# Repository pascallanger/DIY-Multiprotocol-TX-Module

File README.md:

# Multiprotocol TX Module

The **Multiprotocol Tx Module** (or **MULTI-Module**) is a 2.4GHz transmitter module which enables almost any transmitter to control many different receivers and models, including many popular helicopters, planes, quadcopters, and miniquads.

The main forum for protocol requests and questions is on [RCGroups.com](https://www.rcgroups.com/forums/showthread.php?2165676-DIY-Multiprotocol-TX-Module/page10000).

If you like this project and want to support further development please consider making a [donation](docs/Donations.md).  

<table cellspacing=0>
  <tr>
    <td align=center width=200><br><b>€5</b></td>
    <td align=center width=200><br><b>€10</b></td>
    <td align=center width=200><br><b>€15</b></td>
    <td align=center width=200><br><b>€25</b></td>
    <td align=center width=200><br><b>Other</b></td>
  </tr>
</table>

## Development status

Multiprotocol downloads: 

Current Multiprotocol code check status: . Download the latest **test** build [here](https://downloads.multi-module.org/latest-test/).

Current Multiprotocol boards check status: 

## Quicklinks
* [Download latest releases of the firmware](https://github.com/pascallanger/DIY-Multiprotocol-TX-Module/releases) and [instructions to upload .hex files](docs/Advanced_Manually_Setting_ATmega328_Fuses.md)
* [Forum on rcgroups](http://www.rcgroups.com/forums/showthread.php?t=2165676)
* [Available Protocols list](Protocols_Details.md)
* [The old documentation](docs/README-old.md)

## Outline of the documentation
1. Introduction (this page)
1. [Available protocols](Protocols_Details.md)
1. [Transmitters and serial/telemetry options](docs/Transmitters.md)
1. [Module Hardware options](docs/Hardware.md)
1. Compiling and programming the module
    * [Atmega328p Multiprotocol Module](docs/Compiling.md)
    * [STM32 Multiprotocol Module](docs/Compiling_STM32.md)
    * [OrangeRX Module](docs/Compiling_OrangeTx.md)
1. [Transmitter Setup](docs/Transmitters.md) 
    * [Channel Order](docs/Channel_Order.md)
1. [How to for popular models](docs/Models.md)
1. [Troubleshooting](docs/Troubleshooting.md)
2. [Advanced Topics (not for the fainthearted!)](docs/Advanced_Topics.md)

## Introduction
A functioning MULTI-Module consists of (see image below):  

1.  A host RC Tx

1. A Multiprotocol Transmitter Module (MULTI-Module) that connects to a host transmitter.  This module is typically comprised of
   * A microcontroller (currently ATMega328P or STM32) that interfaces with the Tx, controls the module functions and forwards the RC commands to the RF hardware
   * One or more (but at least one) RF modules that provide the capability to communicate with RC receivers.  To communicate with the receiver the RF module in the Tx must match with the RF module type in the receiver.  The four most common 2.4GHz RF chips on the market are supported TI CC2500, Nordic NRF24L01, Cypress CYRF6936, and the Amiccom A7105
   * MULTI-firmware loaded on to the microprocessor.  At a high level, this firmware performs a few different functions: 
     * It interfaces with signals from the host Tx and decodes these for transmission to the model, it manages the activation of the correct hardware RF module for each protocol
     * It implements the unique communication protocols for each receiver/model and manages the all-important binding process with a receiver/model
     * In the case of some protocols (for example DSMX and FrSky) it receives and decodes the telemetry information and makes this available to the radio.
1. The physical 2.4GHz antenna (or in some cases multiple antennas) for the modules

One of the most attractive features of the MULTI-module is the ability to send telemetry signals back to the transmitter. The MULTI-Module is fully telemetry capable for all protocols that support telemetry.  Your ability to use the telemetry information depends on  your radio hardware and firmware.

In constructing a functioning MULTI-Module there are important choices to be made and tradeoffs to be aware of.  The most important are:

## **Choice 1:** Which MULTI-Module hardware option 

There are currently four generic paths to get your hands on an MULTI-Module.  These are outlined in detail on the [hardware](docs/Hardware.md) page.  Here they are, in order of increasing difficulty:
  - **Ready-made MULTI-Module** - Available from Banggood which includes a 4-in-1 RF module and an antenna switcher
  - **DIY MULTI-Module** - Purchase one of the PCB options from [OSHPark](http://www.oshpark.com) and then solder on your own components and RF modules (the two options differ in the MCU used - either an ATmega328P or a STM32F1)
  - **OrangeRx MULTI-Module** You can turn the OrangeRx DSM2/X Tx module (available from HobbyKing) into a MULTI-Module to increase the number of supported protocols, add telemetry as an option and bind more successfully with problematic bind-and-fly models. 
  - **Scratchbuild a MULTI-Module** -  Build the module from scratch using perfboard base, an Arduino Pro Mini and discrete components.

The last option is where it all started and how the pioneers in this project made their boards.  However, due to the growing interest in “one module to rule them all” you now have options to purchase a ready-made board (with old firmware that you will need to upgrade).  

For more information on these options see the [hardware](docs/Hardware.md) page

## **Choice 2:** Which RF modules to include in the MULTI-Module

This depends on your specific needs.  However, recent the availability of the 4-in-1 RF modules from Banggood for less than $35 makes it easy to “have it all”.  Most manufacturers of RC systems (Spektrum, FrSky, FlySky) and toys (Syma, Hubsan, etc.) use one of these four RF chips to manage the RF link between the transmitter and the reciever/model.  Here is an incomplete list of the RF modules and some of the most popular toys that use them.  For the complete list see the [Protocol Details](Protocols_Details.md) page.

|Manufacturer|RF Chip|Example Protocols|
|---|---|---|
|Cyprus Semiconductor|CYRF6936|DSM/DSMX|
|||Walkera Devo|
|||J6Pro|
|Texas Instruments|CC2500|FrSky|
|||Futaba SFHSS|
|Amiccom|A7105|FlySky|
|||FlySky AFHDS2A|
|||Hubsan|
|Nordic Semiconductor|NRF24L01|HiSky|
|||Syma|
|||ASSAN|
|||and most other Chinese models|

For example, if you have no interest in binding your Tx to an model with and FrSky or Futaba SFHSS receiver you do not need to include the CC2500 RF module in your system.

## **Choice 3:** Which protocols to upload to the MULTI-Module

As the list of supported protocols grows even the STM32 ARM microcontroller cannot hold all of the protocols. You can select the protocols you need and complie your own firmware. Fortunately, the process of selecting and compiling is not too difficult and it is fully documented on the [Compiling and Programming](docs/Compiling.md) page. You can also download firmware from the [Multi-Module](https://downloads.multi-module.org) website. These firmware files have been split into two groups, surface "SFC" and air "AIR". You can check which protocols are included in each of these groups in the [Validate.h](Multiprotocol/Validate.h) source file.

In the case of the ATmega328, the memory required by all the possible protocols exceeds the 32KB flash limit considerably. This means that you will need to make a choice of which protocols you will compile into your firmware.

## **Choice 4:** Choosing the type of interface between the MULTI-Module and your radio (PPM or Serial)

The MULTI-Module supports industry standard PPM interface that works with all transmitters with either:  
 - a module bay or
 - a trainer port or
 - any PPM signal that can be accessed inside the Tx.

Most of the older FM radios support the PPM interface.

If you are the owner of a transmitter that supports the er9X/erSky9X or OpenTX firmwares (Frsky Taranis, Horus or the FlySky TH9X or the Turnigy 9X family) you have the additional option to use a serial protocol to communicate between your Tx and the MULTI-Module. (Owners of Walkera Devo transmitters should look at the [Deviation Tx](http://www.deviationtx.com) project for how to achieve the same end goal). This serial protocol does not require any hardware modifications, but will likely require updating the firmware on your radio. For those willing to do this, there are some nice advantages:
  - The model protocol selection, associated parameters, failsafe and binding is done from the Model Settings menu on the Tx
  - For telemetry capable transmitters, the telemetry integration is done seamlessly with the Tx firmware. (Note that FrSky TH9X/Turnigy 9X/R transmitters require a telemetry mod to be done before telemetry can work).  Click on the link corresponding to your Tx on the [Transmitters](docs/Transmitters.md) page for more details.

# How to get started?
1. Browse the [Protocols](Protocols_Details.md) page to see which protocols you would like on your module
1. Go to the [Hardware Options](docs/Hardware.md) page to decide which of the MULTI-Module hardware options appeals to you and which RF modules you plan to integrate
1. Once you have your module, you should review what jumper settings or modifications are required to the module to support serial communication and possibly telemetry
1. Go to [Compiling and Programming](docs/Compiling.md) page to download, compile and program your MULTI-Module
1. Finally, you should visit the setup page for your transmitter by clicking on the link corresponding to your Tx on the [Transmitters](docs/Transmitters.md) page to configure the last few settings before you can fly to your heart’s content!!!!!

# Troubleshooting
Visit the [Troubleshooting](docs/Troubleshooting.md) page.  Please bear in mind that the MULTI-Module is a complex system of hardware and software and it may take some patience to get it up and running.  Also remember that the developers of the system are actual users of the system.  This means that at any moment in time the system is working perfectly for them.  A corollary to this is that if you are struggling there are likely two scenarios.  First, that the problem is with your hardware or with your configuration, second, and much more unlikely but not impossible scenario, is that you are struggling with a new undiscovered bug.  (The author of this documentation speaks from experience ;-)   Please check the RC Groups forum and search for keywords relating to your problem before posting a reply.  When you do post a reply please so humbly and respectfully – you will find many helpful people there.  In your reply please include as much relevant information as possible and attach compilation output and ```_Config.h``` files as text attachments to keep the forum clean.
# A final word
A very big thanks to all the people who have shared their time so graciously to create this great project.  If you come across them on RC Groups, please be kind and show appreciation.  In no particular order:
* Pascal Langer (rcgroups: hpnuts)
* Ben Lye (rcgroups: benzo99)
* Midelic (rcgroups: midelic)
* Mike Blandford (rcgroups: Mike Blandford)
* schwabe - from OpenTX 
* PhracturedBlue – from [Deviation TX project](http://www.deviationtx.com)
* goebish – from [Deviation TX project](http://www.deviationtx.com)
* victzh – from [Deviation TX project](http://www.deviationtx.com)
* hexfet – from [Deviation TX project](http://www.deviationtx.com)

Your help would be greatly appreciated.  If protocol reverse-engineering and dev is not your thing then any help with testing and contributing to the documentation would be amazing.  Given the number of different Tx/module hardware/RF module/protocol/model combinations the process of testing and documenting is a major bottleneck for the developers.  Anything you can do to help will free them up to do even greater things. 

If you like this project and want to support further development please consider making a [donation](docs/Donations.md).

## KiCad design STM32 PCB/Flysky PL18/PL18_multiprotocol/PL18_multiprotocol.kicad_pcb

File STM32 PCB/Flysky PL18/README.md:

# MPM for Flysky PL18

The PCB design is located in PL18_multiprotocol folder and is designed using KiCad 6.0.

The casing is located in Casing folder and is designed using Blender 3.3.1.  The model included 2 pieces, T is the top piece and B is the bottom pieces.  These 2 pieces is cloned into TF and BF respectively to apply all modifiers and make manifold for 3D printing.  I have included the stl files generated for simplity.

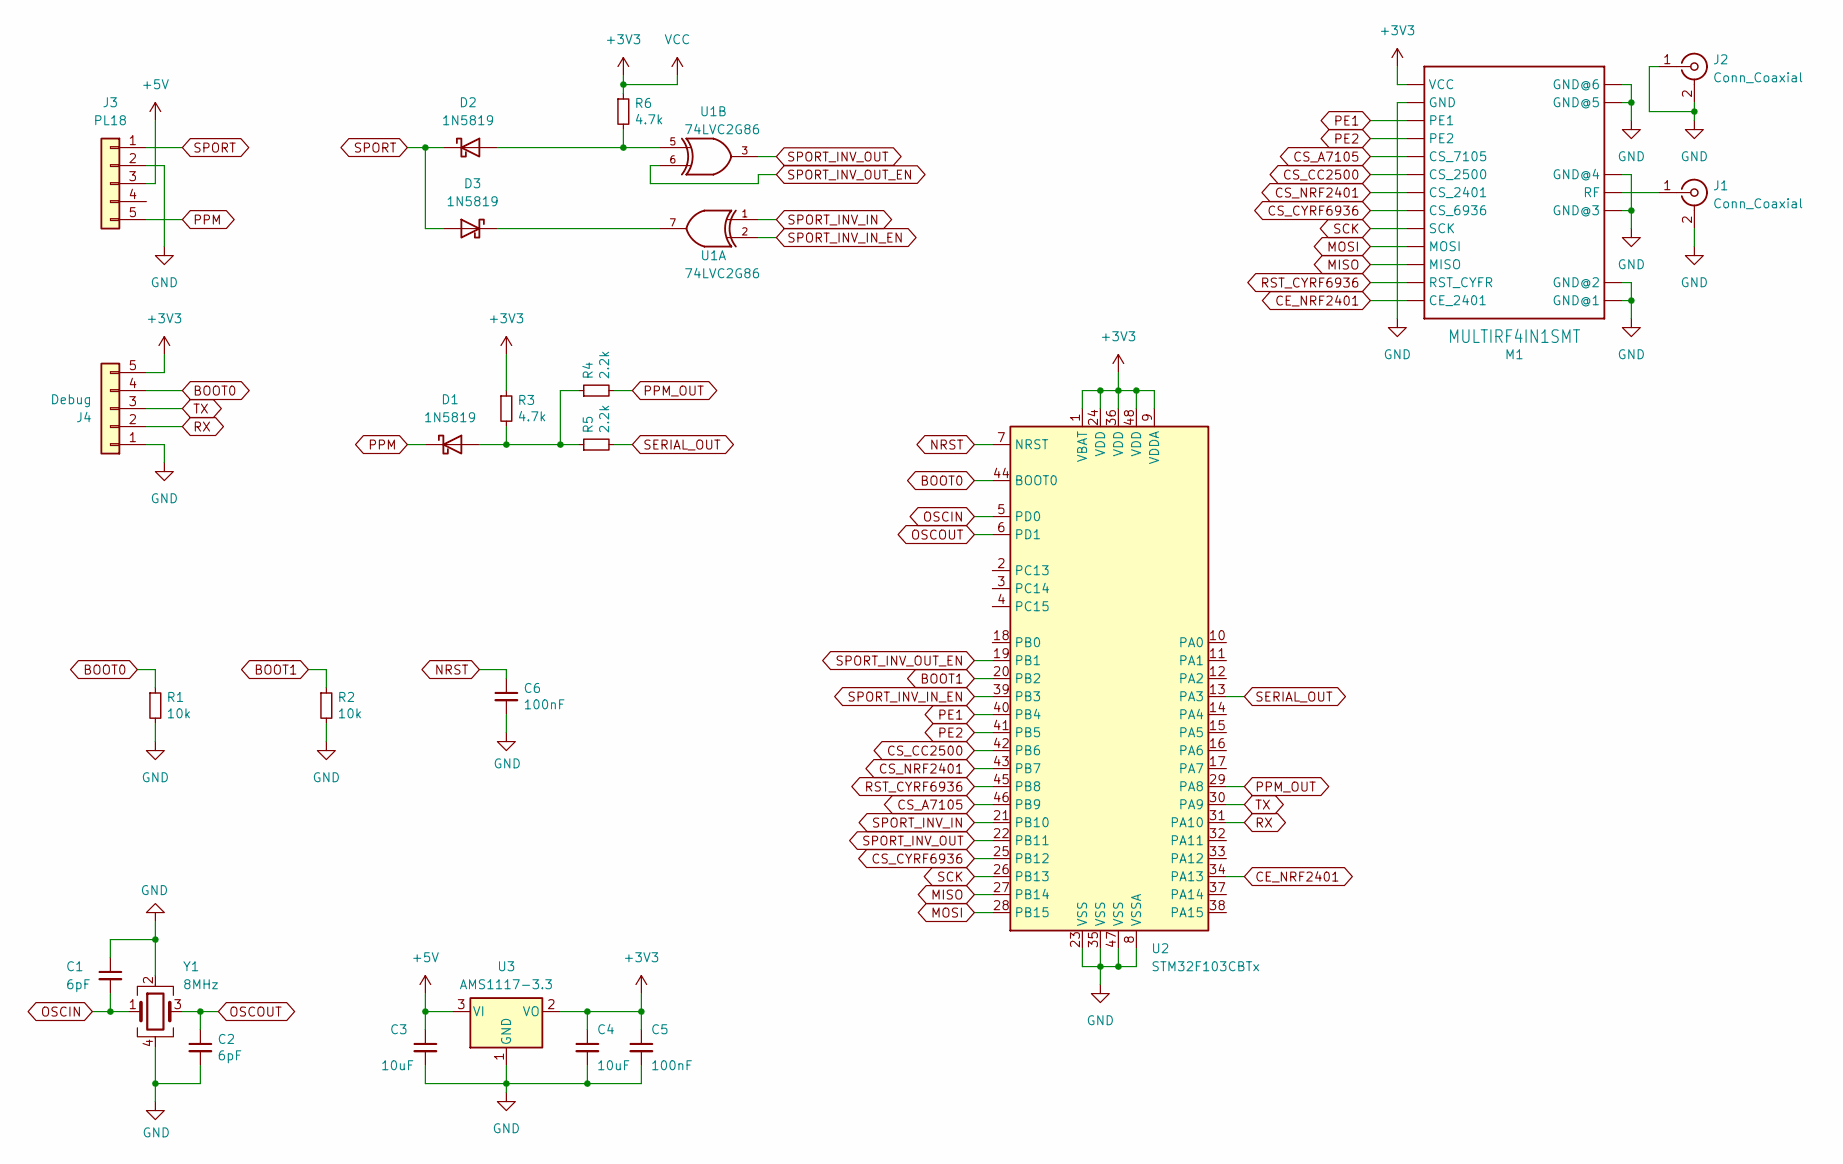
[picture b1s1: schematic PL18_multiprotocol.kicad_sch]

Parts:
C1, C2: 6pF; C_0603_1608Metric_Pad1.08x0.95mm_HandSolder
C3, C4: 10uF; C_0603_1608Metric_Pad1.08x0.95mm_HandSolder
C5, C6: 100nF; C_0603_1608Metric_Pad1.08x0.95mm_HandSolder
D1, D2, D3: 1N5819; D_SOD-123
J1, J2: Conn_Coaxial; MMCX_Molex_73415-1471_Vertical
J3: PL18; DS-B01F-A-S2
J4: Debug; JST_GH_BM05B-GHS-TBT_1x05-1MP_P1.25mm_Vertical
M1: MULTIRF4IN1SMT; MULTIRF4IN1-SMT
R1, R2: 10k; R_0603_1608Metric_Pad0.98x0.95mm_HandSolder
R3, R6: 4.7k; R_0603_1608Metric_Pad0.98x0.95mm_HandSolder
R4, R5: 2.2k; R_0603_1608Metric_Pad0.98x0.95mm_HandSolder
U1: 74LVC2G86; VSSOP-8_3.0x3.0mm_P0.65mm
U2: STM32F103CBTx; LQFP-48_7x7mm_P0.5mm
U3: AMS1117-3.3; SOT-223-3_TabPin2
Y1: 8MHz; Oscillator_SMD_Abracon_ASE-4Pin_3.2x2.5mm

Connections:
+3V3: C4.1, C5.1, J4.5, M1.VCC, R3.1, R6.1, U1.8 (VCC), U2.1 (VBAT), U2.9 (VDDA), U2.24 (VDD), U2.36 (VDD), U2.48 (VDD), U3.2 (VO)
+5V: C3.1, J3.3, U3.3 (VI)
BOOT0: J4.4, R1.1, U2.44 (BOOT0)
BOOT1: R2.1, U2.20 (PB2)
CE_NRF2401: M1.CE_2401, U2.34 (PA13)
CS_A7105: M1.CS_7105, U2.46 (PB9)
CS_CC2500: M1.CS_2500, U2.42 (PB6)
CS_CYRF6936: M1.CS_6936, U2.25 (PB12)
CS_NRF2401: M1.CS_2401, U2.43 (PB7)
GND: C1.1, C2.2, C3.2, C4.2, C5.2, C6.2, J1.2 (Ext), J2.1 (In), J2.2 (Ext), J3.2, J4.1, M1.GND, M1.GND@1, M1.GND@2, M1.GND@3, M1.GND@4, M1.GND@5, M1.GND@6, R1.2, R2.2, U1.4 (GND), U2.8 (VSSA), U2.23 (VSS), U2.35 (VSS), U2.47 (VSS), U3.1 (GND), Y1.2, Y1.4
MISO: M1.MISO, U2.27 (PB14)
MOSI: M1.MOSI, U2.28 (PB15)
NRST: C6.1, U2.7 (NRST)
unnamed: D1.2 (A), R3.2, R4.1, R5.1
unnamed: D2.2 (A), R6.2, U1.5
unnamed: D3.1 (K), U1.7
unnamed: J1.1 (In), M1.RF
OSCIN: C1.2, U2.5 (PD0), Y1.1
OSCOUT: C2.1, U2.6 (PD1), Y1.3
PE1: M1.PE1, U2.40 (PB4)
PE2: M1.PE2, U2.41 (PB5)
PPM: D1.1 (K), J3.5
PPM_OUT: R4.2, U2.29 (PA8)
RST_CYRF6936: M1.RST_CYFR, U2.45 (PB8)
RX: J4.2, U2.31 (PA10)
SCK: M1.SCK, U2.26 (PB13)
SERIAL_OUT: R5.2, U2.13 (PA3)
SPORT: D2.1 (K), D3.2 (A), J3.1
SPORT_INV_IN: U1.1, U2.21 (PB10)
SPORT_INV_IN_EN: U1.2, U2.39 (PB3)
SPORT_INV_OUT: U1.3, U2.22 (PB11)
SPORT_INV_OUT_EN: U1.6, U2.19 (PB1)
TX: J4.3, U2.30 (PA9)

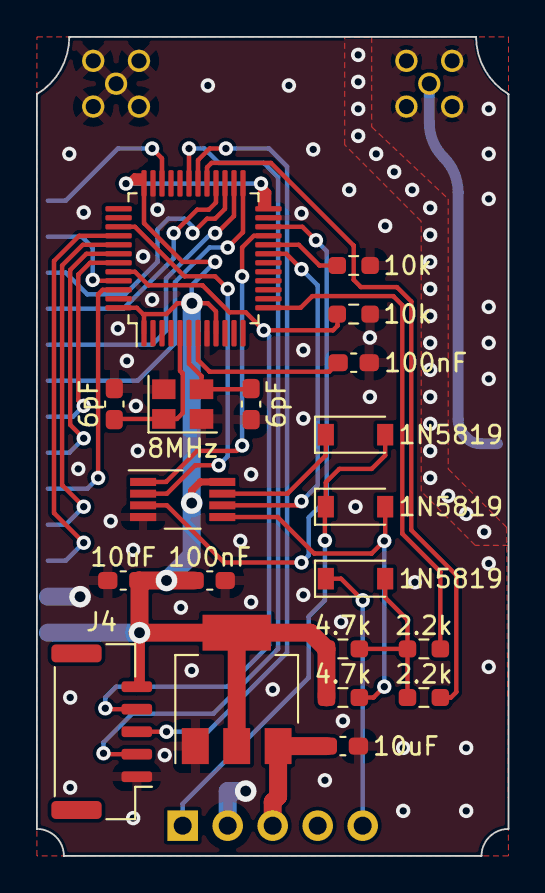
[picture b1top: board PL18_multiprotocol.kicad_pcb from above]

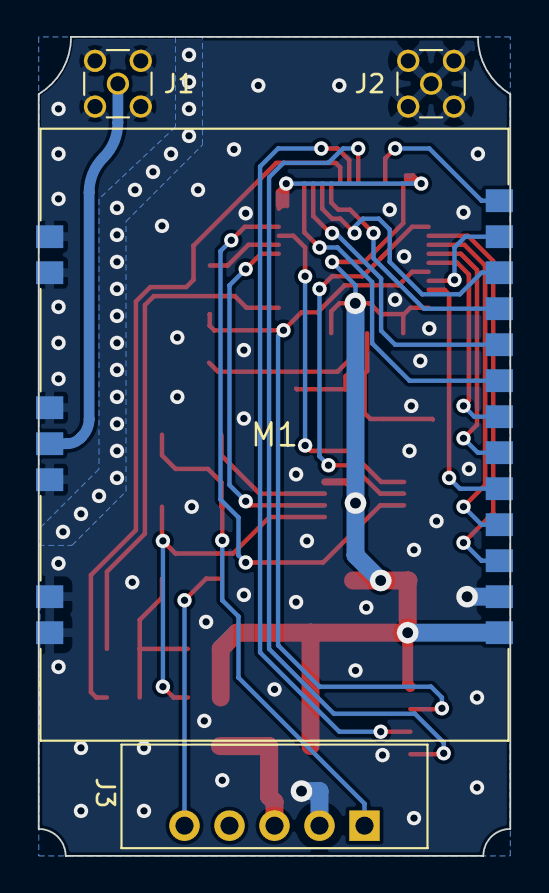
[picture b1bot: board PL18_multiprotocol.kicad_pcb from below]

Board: 2 copper layers, 26.2 x 45.5 mm, 24 parts (4 on the bottom side), 33 nets.

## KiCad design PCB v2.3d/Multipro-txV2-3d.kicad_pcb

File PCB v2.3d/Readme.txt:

These are KiCad files and you are free to do what you will with them. KiCad is a good, free, and fairly
easy to learn.  Build your own BOM and gerber files.

This is a variant of the Multipro V2.3c circuit design.  It is basicly the same as the 2.3c board as far
as component placement goes.  What's changed is the added resistors for the serial protocol and also
the addition of solder jumpers on the bottom of the board for the various options to connect the TX, RX, and PPM
lines through them. See below for more detail.

The schematic has been updated to reflect the added components and jumper pads as well as cleaned
up a little.  As it sits now, the .net file loads without any complaints and DRC checks pass.

The jumpers, and how they are used:

There are four solder type jumpers on the bottom side of the board near the lower left corner when the
bottom of the board is facing towards you. The silkscreen shows which jumper is which. These four jumpers 
enable the board to be configured in several ways as explaned below.

	(J-1)	Use (PPM V/V) if the incoming PPM signal is at a higher voltage level, leave open if ~~5V.

	(J-2)	Use (Jumper 2) to connect the incomming PPM signal to the RX pin on the processor

	(J-3)	Short (TELEM) only if you have done a telemetry mod to your radio, leave open if not needed. When
		connected, pin 2 of the two pin header (P3) is also connected.

	(J-4) Use (MOD) only to connect the transmitter pin 2 to pin 1 of the two pin header (P3).

The direction this project is going, it is most likely J-2 will be the only one needing to be shorted for
the serial method of sending model protocols.

These files are submitted without any guarentee of accureacy or suitability for any intended use.  I am strictly
an amature with time on his hands. Although I have done all I know to make it correct, things outside of my
knowledge base are beyond my control.  Do not use untested equipment around persons not familiar with the hazards
of remote controlled vehicals.

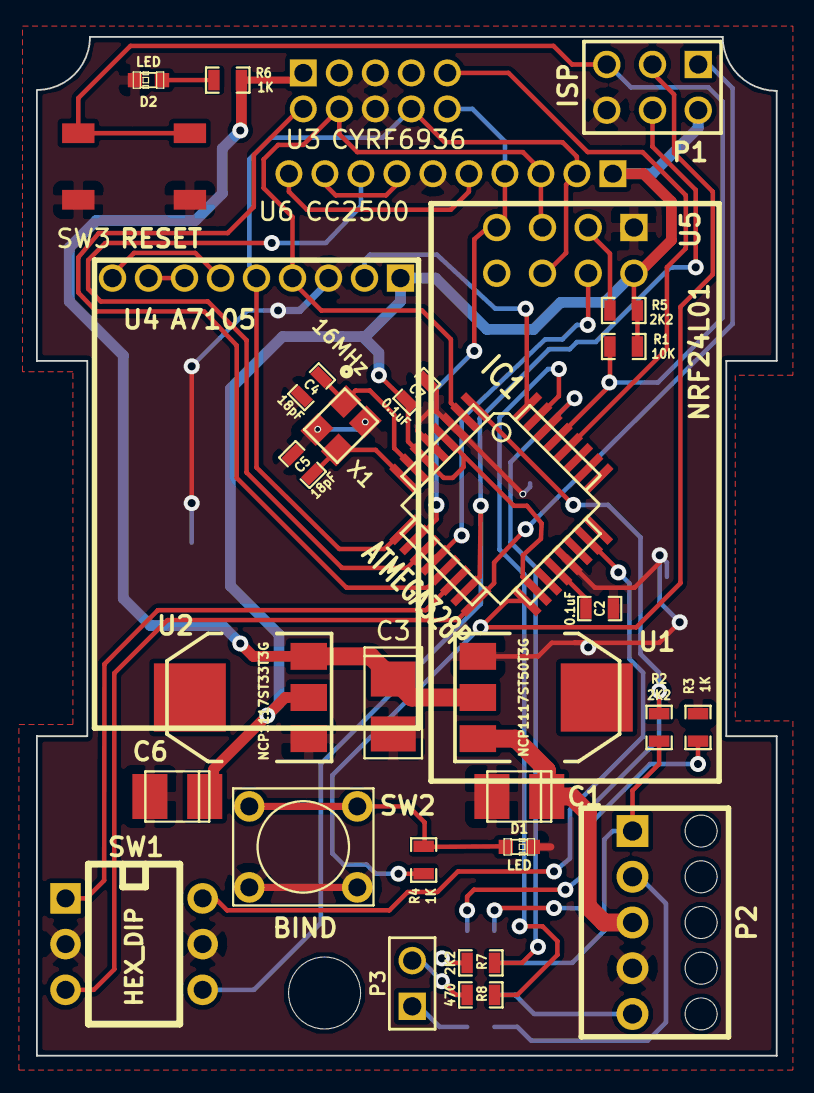
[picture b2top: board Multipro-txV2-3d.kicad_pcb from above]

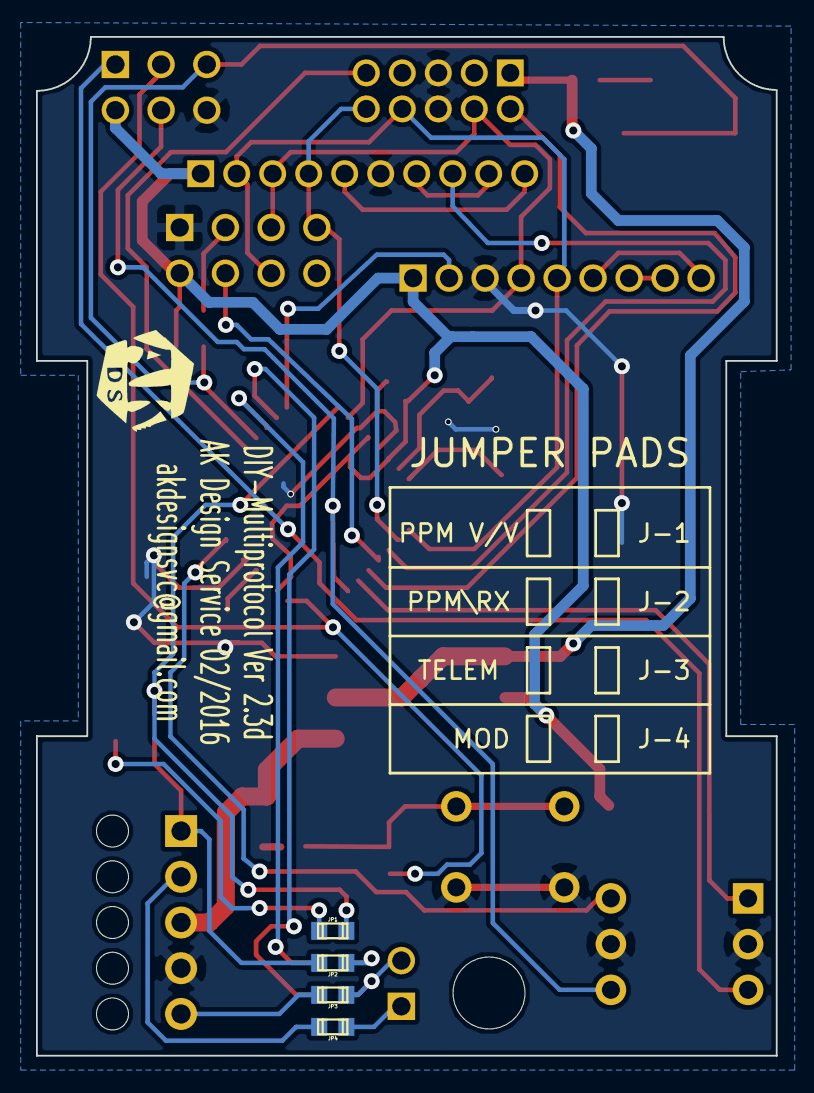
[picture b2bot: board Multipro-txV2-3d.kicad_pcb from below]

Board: 2 copper layers, 41.1 x 56.6 mm, 37 parts (5 on the bottom side), 38 nets.

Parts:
2_3d_jumper_table: VAL**; 2_3d_jumper_table
C1, C3, C6: 22uF; c_tant_B
C2, C7: 0.1uF; SM0603_Capa
C4, C5: 18pF; SM0603_Capa
D1, D2: LED; LED-0603
Hole_4mm: Hole_4mm
IC1: ATMEGA328P; TQFP32
JP1, JP2, JP3, JP4: JUMPER; c_0603
P1: ISP; pin_array_3x2
P2: CONN_5; MOLEX_4455_N2X5
P3: CONN_2; PIN_ARRAY_2X1
R1: 10K; SM0603_Resistor
R2, R5, R7: 2K2; SM0603_Resistor
R3, R4, R6: 1K; SM0603_Resistor
R8: 470; SM0603_Resistor
SW1: HEX_DIP; DIP-6__300
SW2: BIND; SW_PUSH_6x4.5MM
SW3: RESET; Switch_SMT5mm
U1: NCP1117ST50T3G; SOT223
U2: NCP1117ST33T3G; SOT223
U3: CYRF6936
U4: A7105; XL7105-D03B
U5: NRF24L01
U6: CC2500; header_10_2mm
X1: 16MHz; crystal_FA238-TSX3225

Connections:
3V3: C6.1, C7.1, IC1.4, IC1.6, IC1.18, P1.2, R1.1, R5.2, U2.2, U4.1, U5.2, U6.1
+5V: C3.1, R6.1, U1.2, U2.3, U3.1
/A0: IC1.23, SW1.6
/A7105_CSN: IC1.32, U4.2
/BATT: C1.1, P2.3, U1.3
/CC25_CSN: IC1.11, U6.8
/CC25_LANEN: U6.5, U6.10
/CC25_PAEN: U6.7, U6.9
/CYRF_CSN: IC1.13, U3.2
/CYRF_RST: IC1.28, U3.9
/D3: IC1.1, JP1.1, R2.1
/D10: IC1.14, SW1.1
/D11: IC1.15, P1.4, SW1.4
/D12: IC1.16, P1.1, SW1.3
/MISO: IC1.10, U3.10, U5.7, U6.4
/MOSI: IC1.9, U3.8, U4.5, U5.6, U6.2
/NRF_CE: R5.1, U5.3
/NRF_CSN: IC1.12, U5.4
/PB5: IC1.17, P1.3, R4.1
/PPM_IN: JP2.1, P2.1, R2.2
/RESET: IC1.29, P1.5, R1.2, SW3.1, SW3.2
/RX: IC1.30, R7.2
/SCK: IC1.2, U3.4, U4.4, U5.5, U6.3
/TX: IC1.31, R8.2
/xtl1: C4.2, IC1.7, X1.3
/xtl2: C5.1, IC1.8, X1.1
GND: C1.2, C2.2, C3.2, C4.1, C5.2, C6.2, C7.2, D1.2, D2.2, IC1.3, IC1.5, IC1.21, P1.6, P2.4, R3.2, SW1.2, SW1.5, SW2.3, SW2.4, SW3.3, SW3.4, U1.1, U2.1, U3.5, U3.6, U4.3, U5.1, U6.6, X1.2, X1.4
unnamed: D2.1, R6.2
unnamed: U4.7, U4.8
unnamed: U4.6, U4.9
unnamed: JP3.2, P3.2, R8.1
unnamed: JP3.1, P2.5
unnamed: JP4.2, P3.1
unnamed: JP2.2, R7.1
unnamed: JP1.2, R3.1
unnamed: JP4.1, P2.2
unnamed: D1.1, R4.2, SW2.1, SW2.2
unnamed: C2.1, IC1.20

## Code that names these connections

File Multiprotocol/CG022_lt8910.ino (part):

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//
// Hardware wiring:
//   LT8910 RF board connects to MPM breakout pins:
//   - MOSI (PB15) → LT8910 MOSI
//   - MISO (PB14) → LT8910 MISO  
//   - SCK  (PB13) → LT8910 SCK
//   - CS   (PA15/SPI_CSN) → LT8910 CS
//   - 3.3V, GND
//   - RESET (PA14/LT8910_RST) → LT8910 RET pin
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{
	// Deselect all 4-in-1 onboard chips before using the external LT8910.
	// MOSI/MISO/SCK are shared; any chip with CS low would drive the bus.
	#ifdef CC25_CSN_pin
		CC25_CSN_on;
	#endif
	#ifdef NRF_CSN_pin
		NRF_CSN_on;
	#endif
	#ifdef A7105_CSN_pin
		A7105_CSN_on;
	#endif
	#ifdef CYRF_CSN_pin
		CYRF_CSN_on;
	#endif

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
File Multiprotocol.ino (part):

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	// General pinout
	#if defined STM32_board	
	pinMode(CS_pin,OUTPUT);
	pinMode(CC25_CSN_pin,OUTPUT);
	pinMode(NRF_CSN_pin,OUTPUT);
	pinMode(CYRF_CSN_pin,OUTPUT);
	pinMode(CYRF_RST_pin,OUTPUT);
	pinMode(CTRL1,OUTPUT);
	pinMode(CTRL2,OUTPUT);
	#if defined TELEMETRY
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	//pinMode(SCK_pin,OUTPUT);//spi pins initialized with spi init
	//pinMode(SDO_pin,INPUT);			
	pinMode(BIND_pin,INPUT_PULLUP);
	pinMode(PPM_pin,INPUT);
	pinMode(S1_pin,INPUT_PULLUP);//dial switch
	pinMode(S2_pin,INPUT_PULLUP);
	pinMode(S3_pin,INPUT_PULLUP);
	pinMode(S4_pin,INPUT_PULLUP);			
	#else
	DDRD = (1<<CS_pin)|(1<<SDI_pin)|(1<<SCLK_pin)|(1<<CS_pin)|(1<< CC25_CSN_pin);
	DDRC = (1<<CTRL1)|(1<<CTRL2); //output
	DDRC |= (1<<5);//RST pin A5(C5) CYRF output
	DDRB  = _BV(0)|_BV(1);
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	#endif
	
	//**********************************
	//mode_select=0;	// here to test PPM
	//**********************************
	// Update LED
	
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		#endif		
		#endif
		#ifdef STM32_board
		attachInterrupt(PPM_pin,PPM_decode,FALLING);
		#endif
		
		#if defined(TELEMETRY)
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	uint32_t id;
	uint8_t txid[4];
	pinMode(PB0, INPUT_ANALOG); // set up pin for analog input
	pinMode(PB1, INPUT_ANALOG); // set up pin for analog input
	
	if ((EEPROM.read(adress+100)==0xf0) && !create_new)
	{  // TXID exists in EEPROM
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	}
	else
	{ // if not generate a random ID
		randomSeed((uint32_t)analogRead(PB0)<<10|analogRead(PB1));//seed
		//
		id = random(0xfefefefe) + ((uint32_t)random(0xfefefefe) << 16);
		txid[0]=  (id &0xFF);
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ISR(INT1_vect)
#endif
#endif
{	// Interrupt on PPM pin
	static int8_t chan=-1;
	static uint16_t Prev_TCNT1=0;
	uint16_t Cur_TCNT1;
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
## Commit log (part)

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2024-02-22 Improve artifact merge
2024-02-22 Tweak CI job name
2024-02-22 Bump action versions
2024-02-22 Remove CFlie from DIY 5-in-1 AIR
2024-02-22 T18 air, surface, and LBT builds
2024-02-22 Add T-Lite 5-in-1 LBT
2024-02-22 Fix merge
2024-02-23 CI job restructure
2024-02-23 Remove DSMR when MULTI_AIR
2024-02-23 Remove Radiolink/RC4G when MULTI_AIR
2024-02-23 Automated build process updates (#950)
    * 4-in-1 air and surface builds
    * Disable serial and PPM-only builds for STM32 x-in-1
    * More air and surface builds
    * Fix 5-in-1 tests
    * T18 air, surface, and LBT builds
    * Remove CFlie from DIY 5-in-1 AIR
2024-02-23 Bumping revision
2024-02-23 Rename Traxxas/6519 to Traxxas/TQ
2024-02-23 New protocol EazyRC
2024-02-23 EazyRC.1
2024-02-23 EazyRC.2
2024-02-26 Radiolink/RC4G: IDs and RFs
2024-02-28 EazyRC multi IDs/RFs
2024-03-14 Update Protocols_Details.md (#955)
2024-03-14 REALACC multi IDs
2024-03-17 Docs update
2024-03-18 DSM/DSM2SFC new subprotocol
2024-03-19 DSM2SFC timing update
2024-03-21 SGF22: Fix none working IDs
2024-03-22 New protocol Kyosho3/ASF
    Only 1 ID and 1 frequency for now
2024-03-22 Kyosho3: increase bind time to 2.5s
2024-03-23 ASF: try 1
2024-03-25 CYRF6936: Findbestchannels flag addition
2024-03-25 ASF try 2
2024-03-26 ASF try 3
2024-03-26 DSM2_SFC try 1
    Servo refresh rate -> frame rate 16.5/11ms
2024-03-26 DSM2_SFC try 2
2024-03-26 DSM2_SFC try 3
2024-03-29 ASF try 4
2024-03-29 SGF22: new flag
2024-04-02 REALACC: IDs
    Any ID
2024-04-02 Realacc doc update
2024-04-04 Traxxas TQ 6 channels
2024-04-12 SLT try 1
2024-04-12 SLT try 1a
2024-04-13 SLT try 1b
2024-04-14 SLT try 1c
2024-04-14 SLT try 1d
2024-04-15 SLT new sub_protocol V1_4CH
2024-04-18 SLT try 1e
2024-04-26 Traxxas TQ 1st gen: try 1
2024-04-27 Traxxas TQ 1st gen: try 2
2024-05-02 Traxxas TQ 1st gen: try 4
2024-05-04 J6Pro update
2024-05-04 Traxxas TQ 1st gen: try 5
2024-05-17 FX/Q560 new sub protocol
2024-05-21 Update FX/Q560 doc
2024-06-07 New protocol XK2 for the XK A160S
2024-06-14 Disable SCANNER ...
2024-06-14 Disable SCANNER ... (#989)
2024-07-11 E129/C185 new debug flag
2024-07-12 XK2: 1 TX ID but multiple RX IDs?
2024-07-18 chore(ci): bump setup-arduino-ci version to remove nodejs warning
    Gets rid of the numerous "The following actions
    uses Node.js version which is deprecated and will
    be forced to run on node20" warnings
2024-07-18 chore: bump arduino-cli ver
2024-07-18 chore(ci): bump setup-arduino-ci version to remove nodejs warning (#995)
    * chore(ci): bump setup-arduino-ci version to remove nodejs warning
    Gets rid of the numerous "The following actions
    uses Node.js version which is deprecated and will
    be forced to run on node20" warnings
    * chore: bump arduino-cli ver
2024-07-24 Revert main.yml to use the old version of arduino_cli
2024-09-01 add PTF22S - Update SGF22_nrf24l01.ino
2024-09-01 add PTF22S - Update Multi_Protos.ino
2024-09-01 add PTF22S - Update Multiprotocol.h
2024-09-01 add PTF22S - Update _Config.h
2024-09-02 SGF22: new F22S sub protocol
2024-09-26 Update _Config.h
    add sub protocol "J20" to "SGF22" protocol
2024-09-26 Update Multi.txt
    add sub protocol "J20" to "SGF22" protocol
2024-09-26 Update Multi_Protos.ino
    add sub protocol "J20" to "SGF22" protocol
2024-09-26 Update Multiprotocol.h
    add sub protocol "J20" to "SGF22" protocol
2024-09-26 Update SGF22_nrf24l01.ino
    add sub protocol "J20" to "SGF22" protocol
2024-09-26 Update _Config.h (#1019)
    add sub protocol "J20" to "SGF22" protocol
2024-09-26 Update Multi.txt (#1020)
    add sub protocol "J20" to "SGF22" protocol
2024-09-26 Update Multi_Protos.ino (#1021)
    add sub protocol "J20" to "SGF22" protocol
2024-09-26 Update Multiprotocol.h (#1022)
    add sub protocol "J20" to "SGF22" protocol
2024-09-26 Update SGF22_nrf24l01.ino (#1023)
    add sub protocol "J20" to "SGF22" protocol
2024-09-28 Update MT99xx_ccnrf.ino
    add QF009 Su35 support to MT99XX protocol / H7 sub protocol
2024-10-03 Update SGF22_nrf24l01.ino
    Add "FixHeight(Altitude hold)" flag to J20
2024-10-03 Update Multi.txt
    Add SU35 protocol
2024-10-03 Update Multi_Protos.ino
    Add SU35 protocol
2024-10-03 Update _Config.h
    Add SU35 protocol
2024-10-03 Update Multiprotocol.h
    Add SU35 protocol
2024-10-03 Update MT99xx_ccnrf.ino
    Add SU35 protocol
    Pls add in the web page
    https://github.com/pascallanger/DIY-Multiprotocol-TX-Module/blob/master/Protocols_Details.md#MT99XX2---92
    Sub_protocol SU35
    Model: QF009 Su35, CH5 - mode -100% = 6G 100% = 3D, CH6 - LED, CH7 - LED Flash, CH8 - Invert, CH9 - Rate
2024-10-05 Update readme and protocol detals with surface/air info
2025-01-07 V761 Beeper feature on CH10
2025-01-13 YuXiang E190 protocol
    Only 1 ID, bind might not work...
2025-01-15 Yuxiang TX2
2025-01-16 Yuxiang remove CH8
2025-01-17 Yuxiang bind ok
2025-01-18 Yuxiang telemetry
    Offset=7, Ratio=3.5
2025-01-19 Added sub-protocol RF_SIM to the SLT protocol
2025-01-19 fixed typo
2025-01-19 Add RF_SIM sub-protocol to SLT-protocol (#1061)
    * Added sub-protocol RF_SIM to the SLT protocol
    * fixed typo
    ---------
2025-01-19 Update readme and protocol detals with surface/air info (#1034)
    * Update readme and protocol detals with surface/air info
    * Update Protocols_Details.md
    * Update README.md
    ---------
2025-01-19 Traxxas TQ2&TQ1
2025-01-19 Add MT99xx2/SU35 protocol (#1033)
    * Update Multi.txt
    * Update Multi_Protos.ino
    * Update _Config.h
    * Update Multiprotocol.h
    * Update MT99xx_ccnrf.ino
2025-01-19 MT99X2/SU35
2025-01-20 XK2 2nd ID
2025-01-20 XK2 multi IDs
2025-01-21 XK2 details
2025-01-23 QIDI560 new light flag?
2025-01-25 SGF22 Flags trial
2025-01-25 SGF22 FX922 flags
2025-01-27 New car protocol JIABAILE
2025-01-28 New H36 protocol - 1 ID
2025-01-29 JIABAILE RX ID in EEPROM
    Not an autobind protocol anymore.
2025-01-29 Fix DSMR
2025-01-30 Improve DSM telemetry stability?
2025-01-30 Hontai/XKK170 new subprotocol
2025-02-06 New JIABAILE/Gyro subprotocol
2025-02-06 Yuxiang multi IDs/Freqs
2025-02-09 New XK2/P10 sub protocol
2025-02-18 UDIRC new protocol / WIP
2025-02-19 XN297Emu add ReSendPayload
2025-02-21 KAMTOM new surface protocol
    Missing low batt telem
2025-02-22 Update Compiling.md (#1078)
2025-02-22 KAMTOM telemetry
2025-02-24 SHENQI2 new protocol
2025-02-25 SLT2 trial
2025-02-25 SLT2 trial 2
2025-02-25 SLT2 trial 3
2025-02-25 SLT2 last trial?
2025-02-26 SLT2 final
2025-02-26 DSMR SR6200 test 1
2025-02-27 ASF try 1
2025-03-10 New SFC protocol WL91x
2025-03-12 Add FX_QF012 subprotocol (#1091)
2025-03-12 FX/QF012 details
2025-03-12 FX/QF012 details 2
2025-03-12 XK2 Gyro off
2025-03-12 MT99xx Trim channels
2025-03-13 MouldKg multi 6 ports brick support
2025-03-13 MouldKg renamed subprotocols
2025-03-13 FX small changes
2025-03-13 FX telemetry
2025-03-14 MouldKg swap CH5 and CH6
2025-03-20 Added AFHDS2A BS4/BS6 support
2025-03-20 MouldKg update
2025-03-21 FX/QF012 telemetry
2025-03-28 XK2 low batt telemetry
2025-04-02 SGF22 telemetry
2025-04-02 DSMR timing
2025-04-03 Update Protocols_Details.md (#1101)
2025-04-16 SGF22 telem improvement?
2025-05-09 Enable Telemetry on DumbRC receivers
    Tested with X6FGv1.1, X6FP, X6DC(G)v1.1
    I also tested with multiple X6F receivers and some gave RSSI Telem and some gave nothing.
    2 of them had the same PCB as the X6FP and neither gave telemetry.
    I had a third with the same PCB with the X6FP which did give RSSI
    and of my two with an older PCB one gives RSSI telem and the other does not.
    Of the receivers I tried only one set packet_in[6] to match the TX packet[1] and it was the
2025-05-10 Enable Telemetry on DumbRC receivers (#1111)
    Tested with X6FGv1.1, X6FP, X6DC(G)v1.1
    I also tested with multiple X6F receivers and some gave RSSI Telem and some gave nothing.
    2 of them had the same PCB as the X6FP and neither gave telemetry.
    I had a third with the same PCB with the X6FP which did give RSSI
    and of my two with an older PCB one gives RSSI telem and the other does not.
    Of the receivers I tried only one set packet_in[6] to match the TX packet[1] and it was the
2025-07-26 preliminary support for new CX-10
2025-07-27 WPL new protocol
    Only 1 ID
2025-07-27 MT99xx/SU35: removed autobind
2025-07-27 WPL try 2
2025-07-27 use preproc if instead of lang if, use id bytes 2 and 3 instead of 0 and 1, formatting
2025-07-27 preliminary impl of CX-10 proto as sub of SGF22
2025-07-27 WPL 3rd try
2025-07-27 WPL 4th
2025-07-27 WPL 5
2025-07-27 WPL 1 ID
2025-07-28 SGF22/CX10 new subprotocol
    Only 2 IDs
2025-08-25 Wrong ID used for FX (58 instead of 28)
2025-09-16 Fix for no bind on SG F22 variants
2025-12-11 Update XK2_ccnrf.ino
    add stunt flag for SkyViper Vector.
2026-02-14 Update FX_nrf24l01.ino
    add FX_BM26 subprotocol
2026-02-14 Update _Config.h
    add FX_BM26 subprotocol
2026-02-14 Update Multi.txt
    add FX_BM26 subprotocol
2026-02-14 Update Multi_Protos.ino
    add FX_BM26 subprotocol
2026-02-14 Update Protocols_Details.md
    add FX_BM26 subprotocol and "Stunt" in XK2 for SkyViper Vector
2026-05-09 (fix) Remove NCC1701 for space needed to upload correctly to flash
    Although the MULTI_AIR builds are completing successfully for the 128Kb versions, just under the 120808 byte threshold, these builds do not work properly when uploaded to MPM. As different builds nea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
2026-05-09 Add post-build size check for 128KB builds
    Agent-Logs-Url: https://github.com/MRC3742/DIY-Multiprotocol-TX-Module/sessions/866c69d6-fc73-4d47-b3ca-2b36e2f29ec9
2026-05-25 Add T-Smart - Model XBM-37 Protocol Support (#22)
    * Apply XBM-37 protocol changes excluding capture files
    Agent-Logs-Url: https://github.com/MRC3742/DIY-Multiprotocol-TX-Module/sessions/f5cfeacc-2389-482f-bb92-824afdf1639c
2026-06-30 Update Hontai_nrf24l01.ino
    add support of optical flow sensor
2026-06-30 Update Protocols_Details.md
    add support for XK K270 optical flow sensor

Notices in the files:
Multiprotocol.ino:
This project is free software: you can redistribute it and/or modify
it under the terms of the GNU General Public License as published by
the Free Software Foundation, either version 3 of the License, or
(at your option) any later version.
